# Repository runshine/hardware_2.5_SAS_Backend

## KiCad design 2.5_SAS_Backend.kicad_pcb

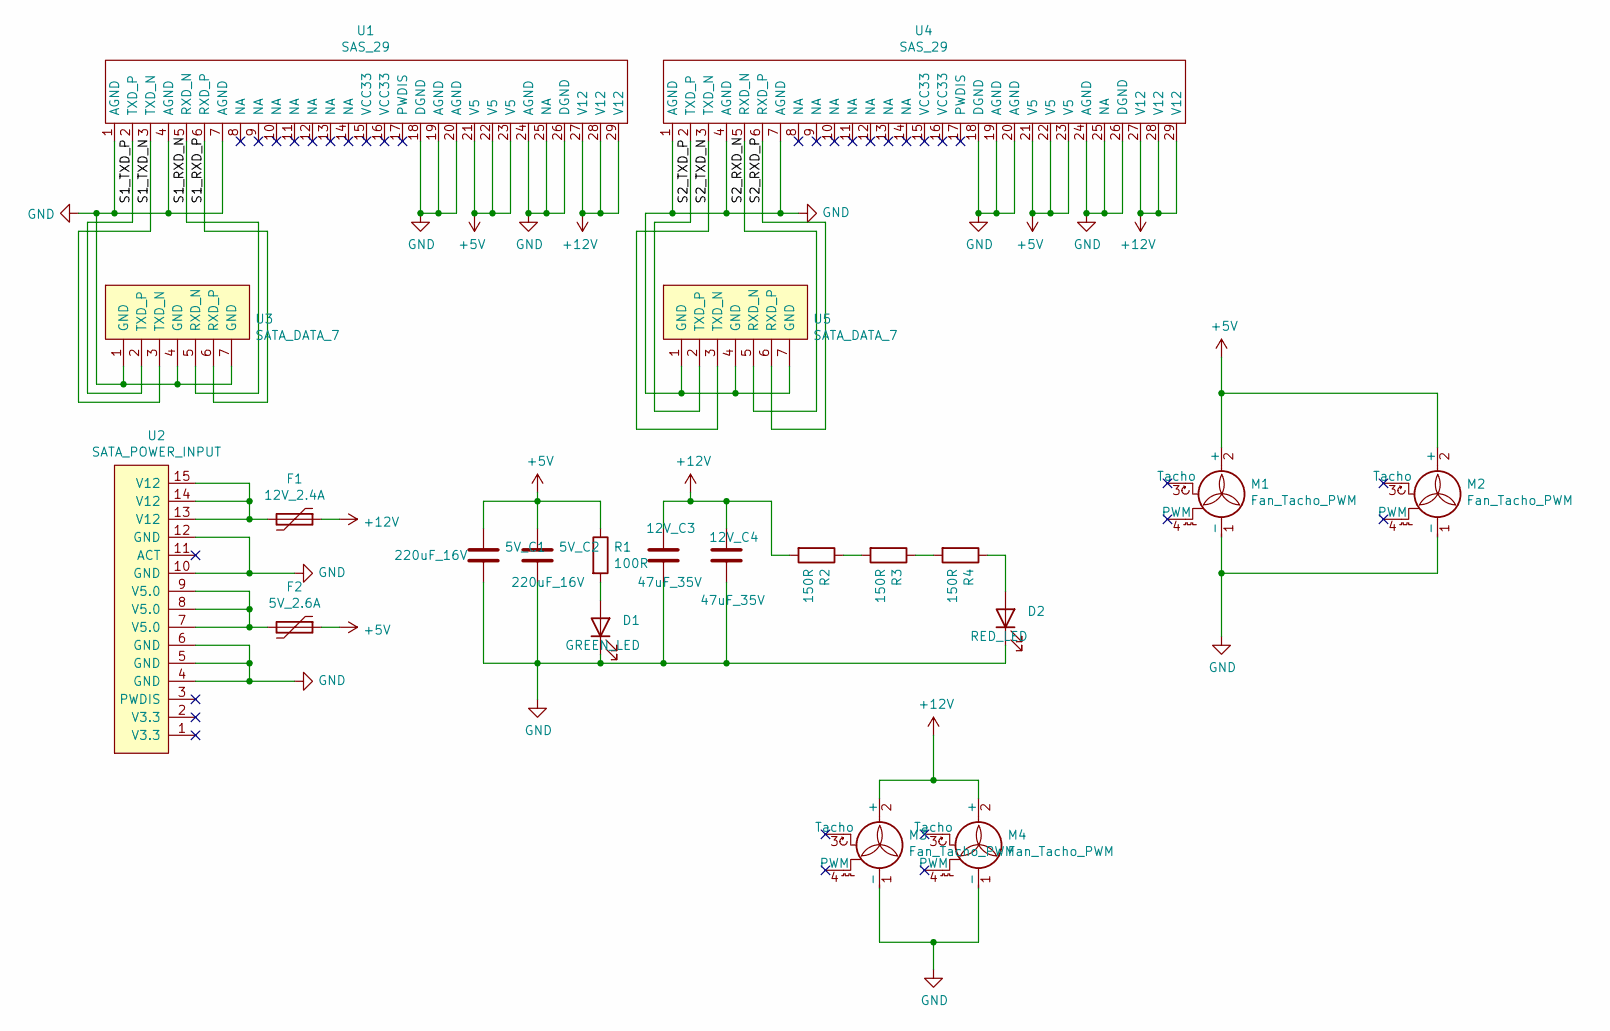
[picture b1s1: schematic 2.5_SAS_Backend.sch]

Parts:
5V_C1, 5V_C2: 220uF_16V; CP_Radial_D5.0mm_P2.50mm
12V_C3, 12V_C4: 47uF_35V; CP_Radial_D5.0mm_P2.50mm
D1: GREEN_LED; LED_0805_2012Metric_Castellated
D2: RED_LED; LED_0805_2012Metric_Castellated
F1: 12V_2.4A; Fuse_1206_3216Metric
F2: 5V_2.6A; Fuse_1206_3216Metric
M1, M2, M3, M4: Fan_Tacho_PWM; FanPinHeader_1x04_P2.54mm_Vertical
R1: 100R; R_0805_2012Metric
R2, R3, R4: 150R; R_0805_2012Metric
U1, U4: SAS_29; SAS_SMD_29P
U2: SATA_POWER_INPUT; SATA_POWER_DIP_15
U3, U5: SATA_DATA_7; SATA_DATA_DIP_A_7

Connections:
+5V: 5V_C1.1, 5V_C2.1, F2.1, M1.2 (+), M2.2 (+), R1.1, U1.21 (V5), U1.22 (V5), U1.23 (V5), U4.21 (V5), U4.22 (V5), U4.23 (V5)
+12V: 12V_C3.1, 12V_C4.1, F1.1, M3.2 (+), M4.2 (+), R2.2, U1.27 (V12), U1.28 (V12), U1.29 (V12), U4.27 (V12), U4.28 (V12), U4.29 (V12)
/S1_RXD_N: U1.5 (RXD_N), U3.5 (RXD_N)
/S1_RXD_P: U1.6 (RXD_P), U3.6 (RXD_P)
/S1_TXD_N: U1.3 (TXD_N), U3.3 (TXD_N)
/S1_TXD_P: U1.2 (TXD_P), U3.2 (TXD_P)
/S2_RXD_N: U4.5 (RXD_N), U5.5 (RXD_N)
/S2_RXD_P: U4.6 (RXD_P), U5.6 (RXD_P)
/S2_TXD_N: U4.3 (TXD_N), U5.3 (TXD_N)
/S2_TXD_P: U4.2 (TXD_P), U5.2 (TXD_P)
GND: 5V_C1.2, 5V_C2.2, 12V_C3.2, 12V_C4.2, D1.1 (K), D2.1 (K), M1.1 (-), M2.1 (-), M3.1 (-), M4.1 (-), U1.1 (AGND), U1.4 (AGND), U1.7 (AGND), U1.18 (DGND), U1.19 (AGND), U1.20 (AGND), U1.24 (AGND), U1.25 (NA), U1.26 (DGND), U2.4 (GND), U2.5 (GND), U2.6 (GND), U2.10 (GND), U2.12 (GND), U3.1 (GND), U3.4 (GND), U3.7 (GND), U4.1 (AGND), U4.4 (AGND), U4.7 (AGND), U4.18 (DGND), U4.19 (AGND), U4.20 (AGND), U4.24 (AGND), U4.25 (NA), U4.26 (DGND), U5.1 (GND), U5.4 (GND), U5.7 (GND)
unnamed: D1.2 (A), R1.2
unnamed: D2.2 (A), R4.1
unnamed: F1.2, U2.13 (V12), U2.14 (V12), U2.15 (V12)
unnamed: F2.2, U2.7 (V5.0), U2.8 (V5.0), U2.9 (V5.0)
unnamed: R2.1, R3.2
unnamed: R3.1, R4.2

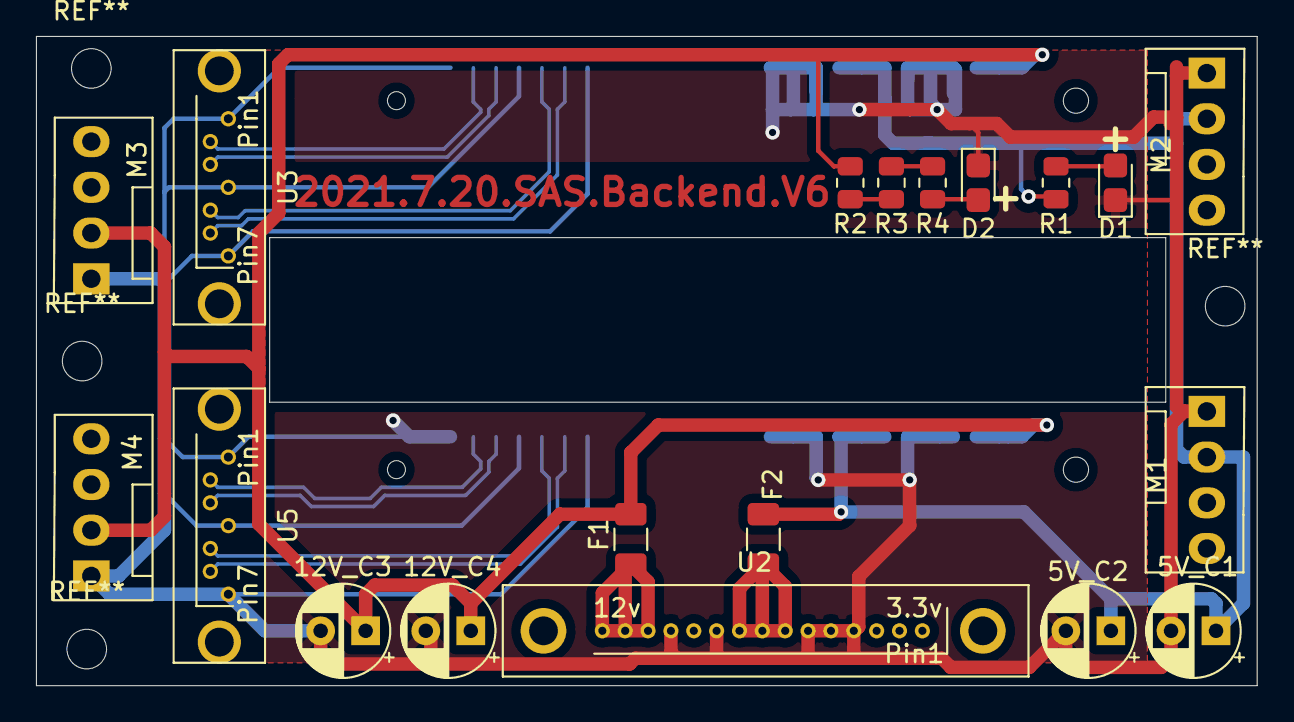
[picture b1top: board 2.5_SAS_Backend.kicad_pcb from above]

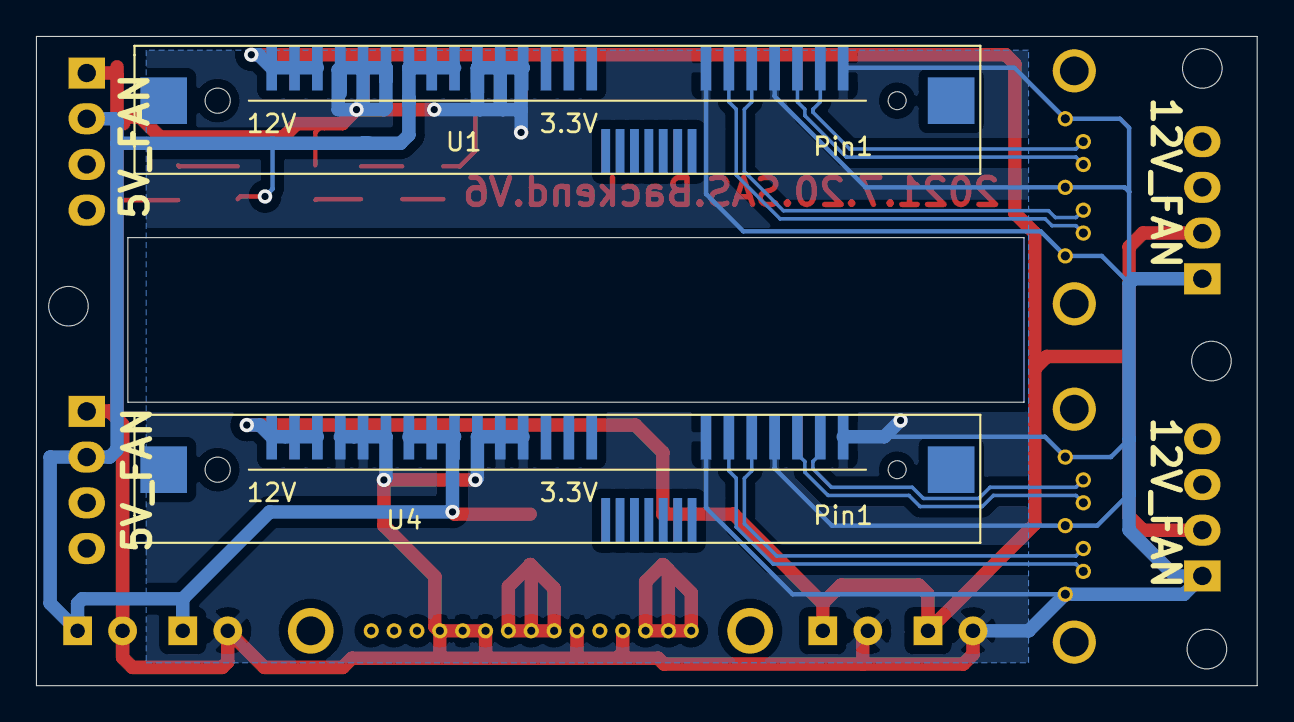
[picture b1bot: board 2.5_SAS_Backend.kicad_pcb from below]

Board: 2 copper layers, 67.8 x 36.1 mm, 21 parts (2 on the bottom side), 17 nets.
